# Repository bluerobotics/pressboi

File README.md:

<div align="center">

# Pressboi

**Dual-Motor Press Control System**

[View Changelog](CHANGELOG.md) • [Download Latest Release](https://github.com/bluerobotics/pressboi/releases/latest)

</div>

---

## Overview

Firmware for the Pressboi dual-motor press control system, built on the Teknic ClearCore platform. This firmware provides precision control for press operations with real-time force monitoring, synchronized dual-motor movement, and network/USB communication.

**Designed to work with:** [BR Equipment Control App](https://github.com/bluerobotics/br-equipment-control-app) - A Python/Tkinter GUI for controlling and monitoring the Pressboi and other Blue Robotics manufacturing equipment.

## Features

- **Dual-motor synchronized control** - Two motors on a single axis for press operations
- **UDP/Ethernet communication** - Network-based control with device discovery
- **USB Serial fallback** - Direct USB communication support
- **Command-based control** - Simple text-based command protocol
- **Real-time telemetry** - Position, force, torque, and status reporting
- **Pause/resume/cancel** - Interrupt and resume operations safely
- **Force monitoring** - Real-time force feedback with configurable limits
- **Auto-generated protocol** - Commands and telemetry from JSON schemas

---

## Building

### Requirements

- **Atmel Studio 7** (Windows) or compatible ARM GCC toolchain
- **Teknic ClearCore libraries** (included as submodules/dependencies)
  - `libClearCore`
  - `LwIP` (Lightweight IP stack)

### Build Instructions

1. Open `pressboi.atsln` in Atmel Studio
2. Ensure libraries are properly referenced:
   - `lib/libClearCore/ClearCore.cppproj`
   - `lib/LwIP/LwIP.cppproj`
3. Select build configuration (Debug or Release)
4. Build the solution (F7)

### Output Files

- `Debug/pressboi.bin` - Binary firmware image
- `Debug/pressboi.uf2` - UF2 format for bootloader flashing

### Flashing

### Via BR Equipment Control App (Recommended for Updates)

The easiest way to update firmware on an already-running device is through the [BR Equipment Control App](https://github.com/bluerobotics/br-equipment-control-app):

1. Open the Firmware Manager in the app
2. Select your device
3. Choose the firmware file or download the latest release
4. Click "Update Firmware" - the app handles the entire flashing process automatically

**Note:** Firmware flashing is only supported over USB connections. For initial flashing of a new device, use the bootloader method below.

### Via Bootloader (For Initial Flashing)

For initial flashing of a new device or when the app is not available:

1. Put the ClearCore into bootloader mode (hold button during power-on)
2. Copy `pressboi.uf2` to the mounted bootloader drive
3. The device will automatically reboot with new firmware

### Via Atmel Studio

1. Connect ClearCore via USB
2. Select "Custom Programming Tool" in project settings
3. Build and program (F5)

---

## Communication Protocol

The firmware uses a simple text-based command protocol over UDP or USB serial:

- Commands: `move_abs <position> mm`, `move_inc <distance> mm`, `home`, `enable`, `disable`
- Status: `DONE: <command>`, `ERROR: <message>`, `INFO: <message>`
- Telemetry: Periodic status updates with position, force, torque, and motor status

See the [BR Equipment Control App](https://github.com/bluerobotics/br-equipment-control-app) for full protocol documentation and command reference.

---

## Hardware Configuration

### Motors
- **Motor A**: Primary press motor (M0)
- **Motor B**: Secondary press motor (M1) - synchronized with Motor A

### Sensors
- **Force sensor**: Load cell or motor torque-based force monitoring
- **Position feedback**: Encoder feedback from ClearPath motors

## Configuration

Key parameters can be configured in `inc/config.h`:

- **Motor parameters**: Steps per mm, velocities, accelerations, torque limits
- **Homing parameters**: Velocities, accelerations, torque limits, backoff distances
- **Force monitoring**: Force limits, sensor calibration, enable/disable options
- **Network settings**: UDP port, packet sizes, telemetry interval

---

## Contributing

For issues, feature requests, or contributions, please open an issue or pull request on GitHub.

---

<div align="center">

⭐ **Star us on GitHub if you found this useful!**

Made with 💙 by the Blue Robotics team and contributors worldwide

---

**[bluerobotics.com](https://bluerobotics.com)** | Manufacturing Equipment Control

</div>

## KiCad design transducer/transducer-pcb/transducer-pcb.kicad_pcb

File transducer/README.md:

# HX711 Force Transducer Interface

Rugeduino (Arduino Uno) firmware for interfacing HX711 load cell amplifier with Pressboi ClearCore controller.

## Hardware Required

- **Ruggeduino-SE ST** (Screw Terminal version - ruggedized Arduino Uno)
- **HX711 Load Cell Amplifier Module**
- **Load Cell** (configured for force measurement)
- 22-24 AWG wire for screw terminal connections

## Wiring

### Load Cell → HX711

```
Load Cell Color    HX711 Pin
---------------    ---------
Red (E+)       →   E+
Black (E-)     →   E-
White (A-)     →   A-
Green (A+)     →   A+
```

### HX711 → Ruggeduino-SE

**Use the screw terminals - no soldering required!**

```
HX711 Pin      Ruggeduino-SE Screw Terminal
---------      ----------------------------
VCC        →   5V
GND        →   GND
DOUT       →   D3
SCK        →   D2
RATE       →   5V (enables 80Hz mode; leave disconnected for 10Hz)
```

### Rugeduino → ClearCore COM-0

**ClearCore COM-0 must be configured in TTL mode!**

```
Ruggeduino-SE Pin    ClearCore COM-0 (8-pin connector)         Wire Color
-----------------    ----------------------------------         ----------
D1 (TX)          →   Pin 8 (Data In / COM0 RX)                 Brown
D0 (RX)          →   Pin 5 (Data Out / COM0 TX)                Green/White
GND              →   Pin 4 (GND)                               Blue
VIN or 5V        →   Pin 6 (5V Power) ⚡ 450mA available       Green
```

**Note:** 
- The ClearCore COM-0 port can power the Ruggeduino-SE directly (up to 450mA available from 5VOB). Connect to VIN or 5V screw terminal. Ruggeduino draws ~50mA typical.
- **During USB programming:** Disconnect D0/D1 from ClearCore to avoid conflicts with USB serial

## Software Setup

### Arduino

1. Install the **HX711 library** by Bogde:
   - Arduino IDE → Tools → Manage Libraries
   - Search "HX711"
   - Install "HX711 by Bogde"

2. Upload `hx711_nano.ino` to the Ruggeduino-SE
   - **Important:** Disconnect D0/D1 from ClearCore during USB upload

3. **Calibrate the scale:**
   - Set `calibration_factor = 1.0` initially
   - Place a known weight (e.g., 10 kg) on the load cell
   - Read the output in Serial Monitor
   - Calculate: `calibration_factor = output_value / 10.0`
   - Update the code and re-upload

### ClearCore

The force sensor is integrated into the pressboi firmware:
- `force_sensor.h` / `force_sensor.cpp` - Force sensor class
- COM-0 configured as TTL UART at 115200 baud
- Force readings automatically appear in telemetry

## Serial Protocol

### Arduino → ClearCore (Continuous Output)

**Format:** Simple floating point value in kg  
**Example:** `12.34\n`  
**Rate:** 80Hz (synchronized with HX711 samples when RATE pin = 5V)

### ClearCore → Arduino (Commands)

| Command | Function |
|---------|----------|
| `T` or `t` | Tare/zero the scale |
| `R` or `r` | Get raw ADC value (for debugging) |
| `C` or `c` | Calibration mode (future) |

## Calibration Procedure

1. **Tare with no load:**
   - Remove all weight from load cell
   - Send 'T' command or power cycle
   - Reading should be ~0.00 kg

2. **Determine calibration factor:**
   - Set `calibration_factor = 1.0` in code
   - Upload to Arduino
   - Place known weight (e.g., 10.00 kg)
   - Read the output value (e.g., 234567)
   - Calculate: `calibration_factor = 234567 / 10.0 = 23456.7`
   - Update code with new factor and re-upload

3. **Verify accuracy:**
   - Test with multiple known weights
   - Adjust calibration factor if needed
   - Typical accuracy: ±0.1% with proper calibration

## Troubleshooting

**No readings:**
- Check wiring connections
- Verify HX711 power (3.3V-5V)
- Check Arduino serial output in Serial Monitor
- Ensure load cell is properly connected

**Noisy/unstable readings:**
- Improve grounding
- Shorten wires between load cell and HX711
- Use shielded cable for load cell wires
- Reduce mechanical vibration

**Readings drift:**
- Allow 10-15 minutes warm-up time
- Reduce temperature variations
- Re-tare periodically

**Readings don't change with force:**
- Check load cell wiring (especially A+/A-)
- Verify load cell is mechanically loaded correctly
- Check calibration factor

## References

- **HX711 Datasheet:** https://cdn.sparkfun.com/assets/b/f/5/a/e/hx711F_EN.pdf
- **HX711 Library:** https://github.com/bogde/HX711
- **SparkFun Hookup Guide:** https://learn.sparkfun.com/tutorials/load-cell-amplifier-hx711-breakout-hookup-guide

## License

MIT License - See main repository LICENSE file

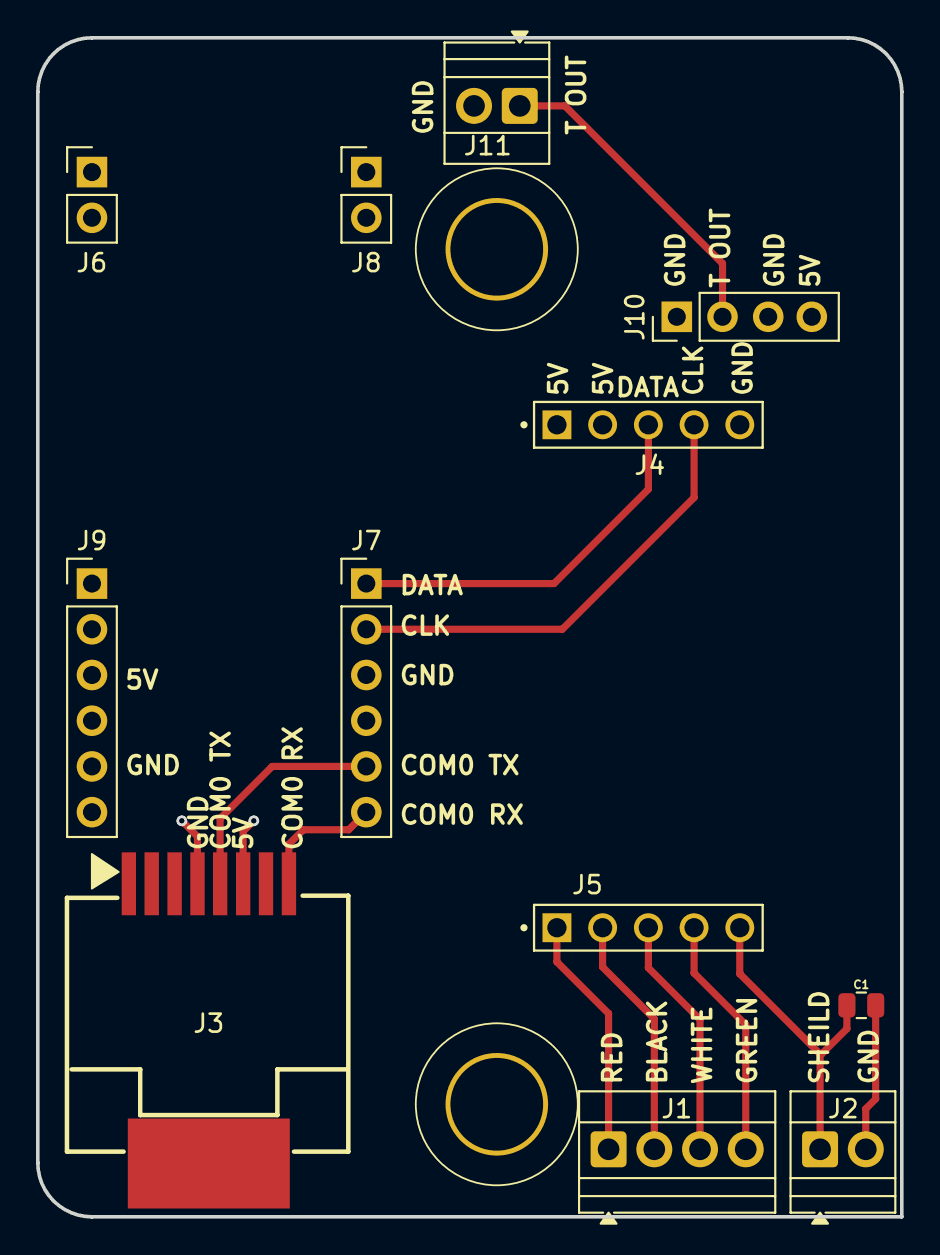
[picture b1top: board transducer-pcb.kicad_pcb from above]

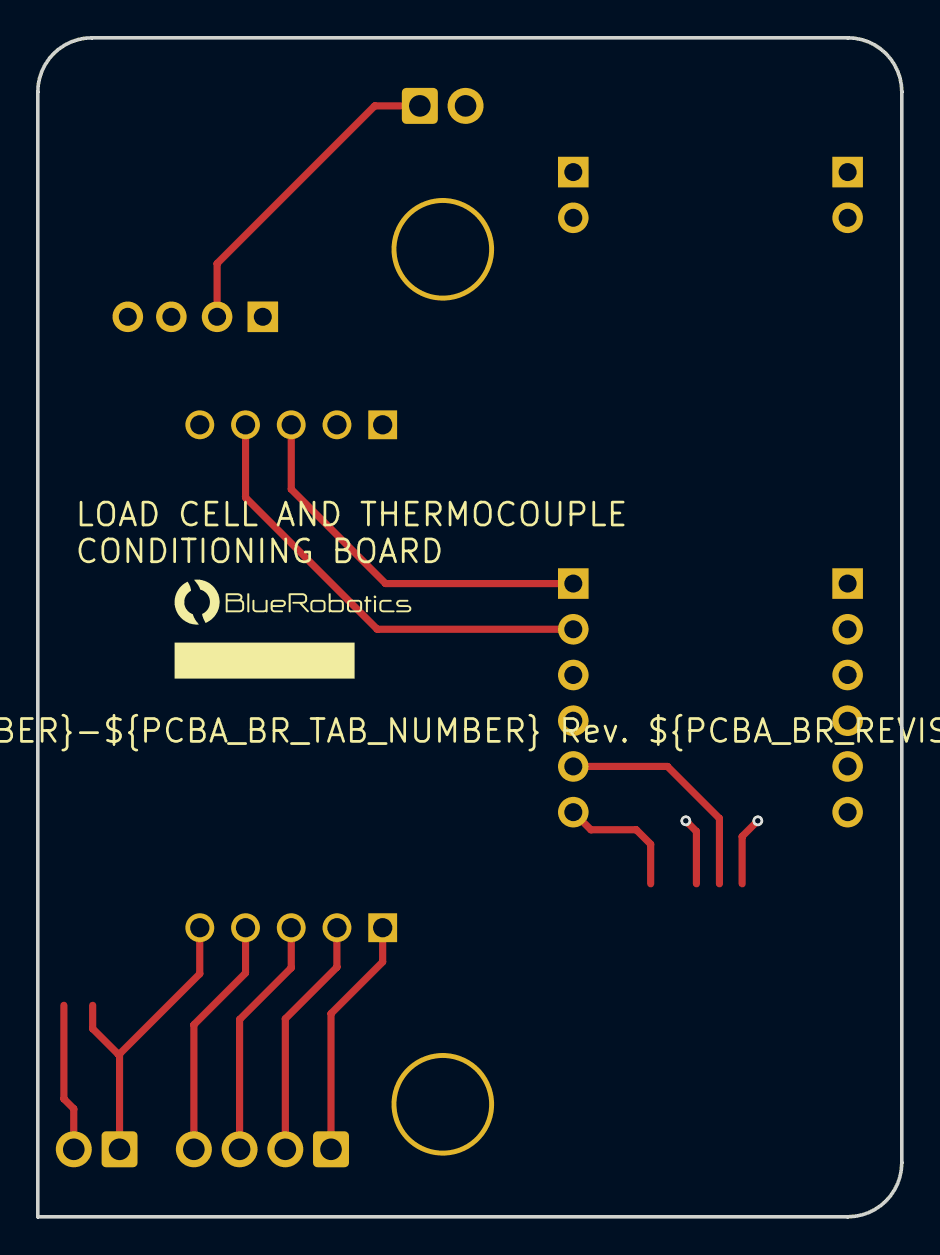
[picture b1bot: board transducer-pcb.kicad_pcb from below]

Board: 4 copper layers, 48.0 x 65.5 mm, 16 parts (2 on the bottom side), 12 nets.

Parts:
C1: 1nF 1kV; C_0805_2012Metric-minimized
GL101: JLC_Number
GL102: BR_Logo
H1, H2: Pressfit_5.15mm_hole; PressFit_5.15mm_hole
J1: Load Cell; DB125-2.54-4P-GN-S
J2: Sheild; KF128-2.54-2P
J3: RJ45; RJ45-SMD_8P-P1.27_RC02015
J4: AMP RIGHT; Pin_Header_1x5_2.54mm_Vertical
J5: AMP LEFT; Pin_Header_1x5_2.54mm_Vertical
J6: NANO UR; PinHeader_1x02_P2.54mm_Vertical
J7: NANO LR; PinHeader_1x06_P2.54mm_Vertical
J8: NANO UL; PinHeader_1x02_P2.54mm_Vertical
J9: NANO LL; PinHeader_1x06_P2.54mm_Vertical
J10: Thermocouple Board; Pin_Header_1x4_2.54mm_Vertical
J11: Thermocouple Out; KF128-2.54-2P

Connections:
/5V: J3.6 (B_N), J4.1, J4.2, J9.3, J10.4
/BLK: J1.2, J5.2
/CLK: J4.4, J7.2
/COM0RX: J3.8 (D_N), J7.6
/COM0TX: J3.5 (C_N), J7.5
/DATA: J4.3, J7.1
/GRN: J1.4, J5.4
/Red: J1.1, J5.1
/T_OUT: J10.2, J11.1
/WHT: J1.3, J5.3
/YLW/SHEILD: C1.1, J2.1, J5.5
GND: C1.2, J2.2, J3.4 (C_P), J4.5, J7.3, J9.5, J10.1, J10.3, J11.2

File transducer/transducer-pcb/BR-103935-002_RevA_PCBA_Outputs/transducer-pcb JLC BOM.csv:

"Comment","Designator","Footprint","JLCPCB Part #"
"0805B102K102CT","C1","BR_Passives:C_0805_2012Metric-minimized","C303890"
"DB125-2.54-4P-GN-S","J1","BR_Connectors:DB125-2.54-4P-GN-S","C918122"
"KF128-2.54-2P","J2","BR_Connectors:KF128-2.54-2P","C474920"
"RC02015","J3","BR_Connectors:RJ45-SMD_8P-P1.27_RC02015","C708654"
"HB-PH3-25415PB2GOP","J4, J5","BR_Connectors:Pin_Header_1x5_2.54mm_Vertical","C6332198"
"PZ254V-11-02P","J6, J8","BR_Connectors:PinHeader_1x02_P2.54mm_Vertical","C492401"
"PZ2.54-1X6P-H25","J7, J9","BR_Connectors:PinHeader_1x06_P2.54mm_Vertical","C42431790"

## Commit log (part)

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2025-10-14 copied over skeleton from fillhead
2025-10-20 simulator and pressboi device updates
2025-10-20 small protocol changes
2025-11-03 Release v1.0.0 - Initial Pressboi firmware
    - Dual-motor press control system
    - UDP/Ethernet + USB Serial communication
    - Command protocol with pause/resume/cancel
    - Real-time telemetry and force monitoring
    - Auto-generated protocol files from JSON schemas
2025-11-03 Enhanced README with comprehensive documentation
    - Added Blue Robotics and Pressboi logos
    - Removed license placeholder
    - Added link to BR Equipment Control App
    - Comprehensive class structure and method reference
    - Detailed protocol documentation
    - Complete architecture overview
2025-11-03 Add comprehensive Microchip Studio flashing instructions
    - Added Atmel ICE method as recommended for development
    - Added USB/BOSSA method via Microchip Studio
    - Reorganized flashing section with clear method priorities
    - Added debugging workflow instructions
2025-11-03 Move Blue Robotics logo to footer
2025-11-03 Add MIT License and update badges
2025-11-03 Fix release badge for private repo
2025-11-03 Switch to dynamic badges now that repo is public
2025-11-03 Update header formatting to match br-equipment-control-app style
2025-11-03 Standardize DONE messages to just command name
    All DONE messages now send just the command name:
    - enable -> 'PRESSBOI_DONE: enable'
    - disable -> 'PRESSBOI_DONE: disable'
    - home -> 'PRESSBOI_DONE: home'
    - move_abs -> 'PRESSBOI_DONE: move_abs'
    - move_inc -> 'PRESSBOI_DONE: move_inc'
2025-11-03 Fix: Remove unused doneMsg variable
2025-11-03 Add abort and clear_errors commands to command parser
    - Added CMD_ABORT and CMD_CLEAR_ERRORS to commands enum
    - Added handlers in dispatchCommand
    - Standardized DONE messages: 'abort' and 'clear_errors'
    - Allow CLEAR_ERRORS to execute in ERROR state
2025-11-03 Standardize clear_errors DONE message
2025-11-03 Refactor: abort removed, cancel handles stopping, reset replaces clear_errors
    - Removed CMD_ABORT - cancel command now handles emergency stops
    - Renamed clear_errors to reset (CMD_RESET)
    - Cancel command now calls abort() to stop motion
    - Reset command sends 'PRESSBOI_DONE: reset'
    - Updated error state to allow CMD_RESET
2025-11-03 Release v1.1.0 - Command improvements and telemetry fixes
2025-11-03 Update binaries for v1.1.0 release
2025-11-04 Add FORCE_SENSOR_ENABLED config flag to support machines without force transducers
2025-11-05 Update README with FORCE_SENSOR_ENABLED configuration instructions
2025-11-05 v1.2.1 - Force sensor configuration and telemetry (missing files)
2025-11-06 Release v1.3.0
    - Added hardware watchdog timer (SAMD51 WDT) with 128ms timeout
    - Added STATE_RECOVERED for watchdog timeout handling
    - Added test_watchdog command for system testing
    - Added motor torque force limiting (no load cell required)
    - Added torque-to-force conversion (Torque% = 0.0335 Ã— kg + 1.04)
    - Added force_mode parameter (motor_torque or load_cell)
2025-11-07 Release 1.4.1
2025-11-13 Document set_force_zero command
2025-11-13 Fix critical NVM byte offset bug and implement missing commands
    - Fixed NVM location indexing: NvmLocations enum uses BYTE offsets, not word indices
    All NVM reads/writes were using wrong offsets (0,1,2,3 instead of 0,4,8,12)
    - Implemented dump_nvm command with proper hex dump display and calibration summary
    - Implemented reset_nvm command to erase all NVM locations
    - Implemented set_force_zero command for both load cell and motor torque modes
    - Fixed ForceSensor tare() - Rugeduino no longer supports tare command
2025-11-14 Release v1.5.0: USB serial communication and lowercase status text
2025-11-14 Update workflow name to include version
2025-11-14 Fix workflow run name syntax
2025-11-14 Add 'abort' option to move_abs force_action parameter
2025-11-14 Add safety timeouts and iteration limits to prevent blocking operations
2025-11-14 Use home position (0mm) as default retract position if not explicitly set
2025-11-14 Reduce network link timeout to 100ms to prevent watchdog timeout during startup
2025-11-14 Feed watchdog during network initialization to prevent startup timeout
2025-11-14 Initialize watchdog after comms setup to avoid timeout during network initialization
2025-11-15 Add endpoint variable to track position where moves end or force triggers
2025-11-15 CRITICAL FIX: Clear force_action before starting retract to prevent infinite loop and watchdog timeout
2025-11-15 Fix abort action to only retract when force limit is hit, not on normal completion
2025-11-15 Release v1.6.0: Add endpoint telemetry, fix infinite retract loop and abort behavior
2025-11-15 Increase watchdog timeout from 128ms to 256ms to prevent false triggers during startup
2025-11-15 Fix TX queue processing to handle multiple messages per loop iteration
2025-11-15 Revert to 1 message per loop - watchdog is fed every iteration so this is fine
2025-11-15 Remove JDBG debug messages from joule integration
2025-11-15 Fix set_retract bug: use LONG_MIN sentinel instead of 0 to detect unset retract position
2025-11-15 Add finer-grained watchdog breadcrumbs for communication functions
2025-11-15 Disable watchdog before rebooting to bootloader to prevent timeout during firmware flash
2025-11-15 Handle zero-step moves gracefully by returning DONE immediately
2025-11-17 Simplify changelog wording for infinite retract loop fix
2025-11-17 Reorganize repository structure: move libraries to lib folder and flatten pressboi subfolder
2025-11-17 v1.6.1: Repository restructuring and README updates
2025-11-18 v1.7.0: Move device definition to firmware repo, fix retract_pos telemetry
2025-11-18 Add v1.7.0 firmware binaries
2025-11-18 Keep only bin, elf, and uf2 in repo
2025-11-18 Update v1.7.0 binaries
2025-11-19 v1.8.0 - USB buffer deadlock fix and device naming portability
2025-11-19 Fix pressboi_conn_tracer widget destruction error
2025-11-19 Fix USB host detection - mark connected when commands received
    - Move USB health tracking from static variables to class members
    - Implement notifyUsbHostActive() to immediately mark host as connected
    - Call notifyUsbHostActive() when USB commands are received
    - Prevents firmware from staying in 'host disconnected' state after app restart
    - Version bump to 1.8.1
2025-11-19 Add debug messages for USB host detection state changes - v1.8.2
2025-11-19 build
2025-11-19 Add changelog entries for v1.8.1, v1.8.2, and v1.8.3
2025-11-19 Fix USB host detection to run every loop iteration
    - Moved USB buffer health check outside message queue processing
    - Health check now runs every loop regardless of queue state
    - Prevents firmware staying in 'disconnected' state after app restart
    - Eliminates need for power cycling microcontroller
    Version: 1.8.5
2025-11-19 Add additional_done_on to move commands
    - Declares that move_abs/move_inc with force_action=retract will send additional retract DONE
    - Moves device-specific behavior into device definition
    - Enables generic script processor to handle this without hardcoded logic
2025-11-19 Firmware v1.9.0 - Smart multi-step command completion
    - Commands with retract action now send single DONE when fully complete
    - Send INFO when move completes, DONE when retract finishes
    - Firmware tracks original command through multi-step sequences
    - Eliminates need for app to handle multi-DONE logic
    - Works for both normal completion and force limit triggers
2025-11-20 Add comprehensive error logging and USB recovery
    - Add ErrorLog system (100 entries, 8.8KB circular buffer) with DEBUG/INFO/WARN/ERROR/CRITICAL levels
    - Add HeartbeatLog (2880 entries, 23KB) for compact 24-hour USB/network status tracking
    - Add dump_error_log command to retrieve diagnostic logs over network/USB
    - Implement USB recovery mechanism: auto-detect stuck buffer and reset port
    - Fix watchdog timeout during USB recovery by feeding watchdog and removing blocking delay
    - Add 500ms fault detection grace period after clearing motor faults
2025-11-20 Update compiled binaries and add Python cache to gitignore
2025-11-20 Remove License section from README (LICENSE file still present)
2025-11-20 Fix compilation: move breadcrumb definitions to config.h header
    Moved WD_BREADCRUMB_* definitions from pressboi.cpp to config.h
    so they are visible to all source files including comms_controller.cpp.
    This fixes compilation errors:
    - WD_BREADCRUMB_USB_RECONNECT was not declared
    - WD_BREADCRUMB_USB_SEND was not declared
    - WD_BREADCRUMB_USB_RECOVERY was not declared
2025-11-20 Release v1.10.1
2025-11-21 Bump version to 1.10.2
2025-11-21 Aggressively reduce packet limits to 1 per call + add motor update breadcrumb
    - Reduced MAX_UDP_PACKETS_PER_CALL from 3 to 1
    - Reduced MAX_PACKETS_PER_CALL (network) from 3 to 1
    - Added WD_BREADCRUMB_MOTOR_UPDATE inside updateState() for granular debugging
    - Even 3 packets per call was causing 128ms+ cumulative time on USB reconnection
    - 1 packet per call is extremely conservative but necessary for reliability
    - Network throughput further reduced but watchdog protection maximized
2025-11-21 Add extensive breadcrumbs throughout firmware for precise timeout diagnosis
    Added breadcrumbs to:
    - enqueueRx, enqueueTx (0x1D, 0x11)
    - processTxQueue sections (0x14-0x17)
    - processUdp packet read (0x1C)
    - processUsbSerial (0x1E-0x1F)
    - dispatchCommand, parseCommand (0x18-0x19)
2025-11-21 Fix TX queue overflow when dumping logs
    - Temporarily disable watchdog during dump_error_log command
    - Log dumps can take >500ms for large logs (100+ entries)
    - Watchdog timeout is only 100ms - would cause reset mid-dump
    - Watchdog is ONLY disabled for this diagnostic command
    - Add 5ms delay per error entry to prevent TX queue overflow
    - Add 50ms delay every 10 heartbeat entries to prevent overflow
2025-11-21 Bump version to 1.10.5
2025-11-22 Add compiled binaries for v1.11.0
2025-11-24 Add polarity to NVM dump output and update version to 1.11.2
2025-11-26 v1.11.3: Increase watchdog timeout to 256ms and optimize USB chunking
    - Increased watchdog timeout from 128ms to 256ms for better stability
    - Reduced USB chunk timeout from 10ms to 3ms to prevent blocking
    - Prevents watchdog timeouts during USB reconnection on app restart
    - Total USB blocking time now ~30ms (well within 256ms watchdog limit)
2025-11-26 Add v1.11.3 compiled binaries
2025-11-26 build: Update firmware to v1.12.0 with home_on_boot and NVM retract persistence
2025-11-26 fix: Delay auto-homing by 2s after boot to prevent watchdog timeout during app restart
    Critical fix for watchdog timeout issue that occurred when app restarted and triggered
    immediate auto-homing. The 2-second delay allows USB/network to stabilize and message
    queues to clear before initiating the homing sequence.
    Fixes #watchdog-on-restart
2025-11-26 build: Add v1.12.1 firmware binaries
2025-11-26 v1.13.0: Operator view enhancements
2025-11-28 v1.14.0: Press report system and strain calibration commands
2025-11-28 Add toggle button for polynomial fit trace (hidden by default)
2026-02-19 Add PCB for load cell adapter
2026-03-10 Rev B PCBA and move arduino file to folder
2026-03-18 v1.14.1: Fix NVM address calculation, telemetry hardcodes, dead code cleanup
    Fix setMachineStrainCoeffs() NVM address to use (8+i)*4 stride,
    replace hardcoded torque offset/scale with member variables and
    correct 2000N clamp, remove unused USB mirror declarations from
    CommsController.
    Made-with: Cursor
2026-03-18 build: Update debug binaries
    Made-with: Cursor
